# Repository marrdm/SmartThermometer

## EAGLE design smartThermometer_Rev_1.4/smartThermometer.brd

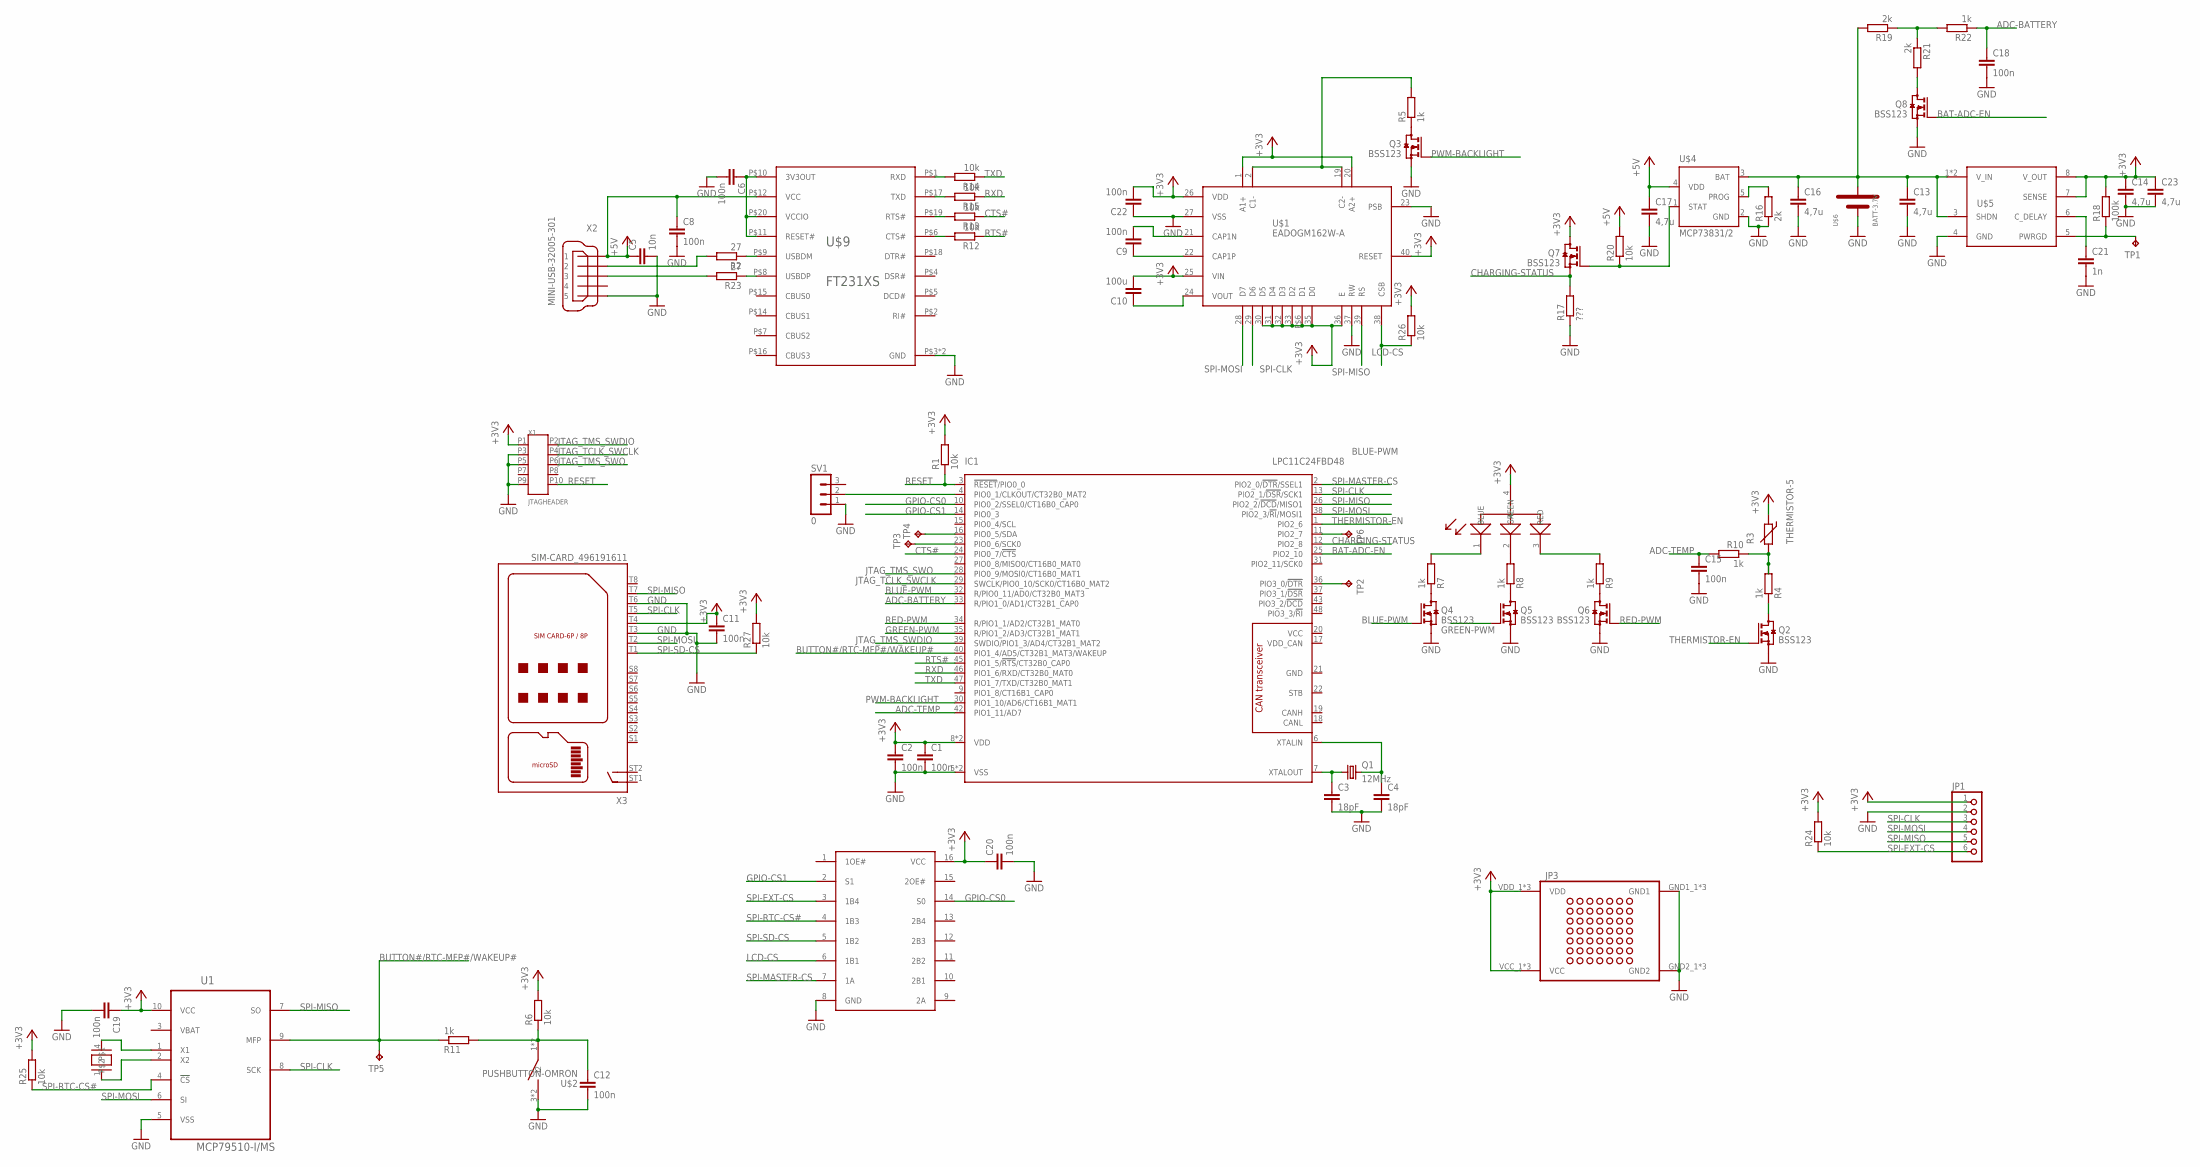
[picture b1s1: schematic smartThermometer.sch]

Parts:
C1, C2, C6, C8, C9, C11, C12, C15, C18, C19, C20, C22: 100n; C0603
C3, C4: 18pF; C0603
C5: 10n; C0603
C10: 100u; C0603
C13, C14, C16, C17, C23: 4,7u; C0805
C21: 1n; C0603
IC1: LPC11C24FBD48; SOT313-2
JP1: PINHD-1X6; 1X06
JP3: PROTOTYPE_2U_SMALL; PROTOTYPE8X6
Q1: 12MHz; HC49UP
Q2, Q3, Q4, Q5, Q6, Q7, Q8: BSS123; SOT23
R1, R6, R12, R13, R14, R15, R20, R24, R25, R26, R27: 10k; R0603
R2, R23: 27; R0603
R3: THERMISTOR-5; R-5
R4, R5, R7, R8, R9, R10, R11, R22: 1k; R0603
R16, R19, R21: 2k; R0603
R17: ???; R0603
R18: 100k; R0603
SV1: 0; MA03-1
TP1: TPTP18SQ; TP18SQ
TP2, TP3, TP4, TP5, TP6: TPTP16SQ; TP16SQ
U1: MCP79510-I/MS; SOP50P490X110-10N
U$1: EADOGM162W-A; LCD_FOOTPRINT
U$2: PUSHBUTTON-OMRON; PUSHBUTTON-OMRON-B3FS-4002P
U$3: LED-RGB-EVERLIGHT
U$4: MCP73831/2; SOT23-5L
U$5: MCP1725; SO08
U$6: BATT-3.7V; MA02-1+-
U$7: CRYSTAL-32.768KHZ-GEYER; 32.768KHZ
U$8: DEMUX-1-4-NXP; TSSOP16
U$9: FT231XS; SSOP20
X1: JTAGHEADER; HEADER10
X2: MINI-USB-32005-301; 32005-301
X3: SIM-CARD_496191611

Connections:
+3V3: C1.1, C2.1, C10.2, C11.1, C14.1, C19.1, C20.1, C22.2, C23.1, IC1.8 (VDD), IC1.44 (VDD), JP1.1, JP3.VCC_1 (VCC), JP3.VCC_2 (VCC), JP3.VCC_3 (VCC), JP3.VDD_1 (VDD), JP3.VDD_2 (VDD), JP3.VDD_3 (VDD), Q7.3 (D), R1.2, R3.1, R6.2, R18.2, R24.2, R25.2, R26.2, R27.2, U1.10 (VCC), U$1.1 (A1+), U$1.20 (A2+), U$1.25 (VIN), U$1.26 (VDD), U$1.30 (D5), U$1.31 (D4), U$1.32 (D3), U$1.33 (D2), U$1.35 (D0), U$1.36 (E), U$1.40 (RESET), U$1.P$6 (D1), U$3.4, U$5.7 (SENSE), U$5.8 (V_OUT), U$8.16 (VCC), X1.P1, X3.T4
+5V: C5.1, C8.1, C17.1, R20.2, U$4.4 (VDD), U$9.P$12 (VCC), X2.1
ADC: R3.2, R4.2, R10.1
ADC-BATTERY: C18.1, IC1.33 (R/PIO1_0/AD1/CT32B1_CAP0), R22.1
ADC-TEMP: C15.1, IC1.42 (PIO1_11/AD7), R10.2
BAT-ADC-EN: IC1.25 (PIO2_10), Q8.1 (G)
BLUE-PWM: IC1.32 (R/PIO0_11/AD0/CT32B0_MAT3), Q4.1 (G)
BUTTON#/RTC-MFP#/WAKEUP#: IC1.40 (PIO1_4/AD5/CT32B1_MAT3/WAKEUP), R11.1, TP5.TP, U1.9 (MFP)
CHARGING-STATUS: IC1.12 (PIO2_8), Q7.2 (S), R17.2
CTS#: IC1.24 (PIO0_7/!CTS!), R13.1
GND: C1.2, C2.2, C3.2, C4.2, C5.2, C6.2, C8.2, C11.2, C12.2, C13.2, C14.2, C15.2, C16.2, C17.2, C18.2, C19.2, C20.2, C21.2, C22.1, C23.2, IC1.5 (VSS), IC1.21 (GND), IC1.41 (VSS), JP1.2, JP3.GND1_1 (GND1), JP3.GND1_2 (GND1), JP3.GND1_3 (GND1), JP3.GND2_1 (GND2), JP3.GND2_2 (GND2), JP3.GND2_3 (GND2), Q2.2 (S), Q3.2 (S), Q4.2 (S), Q5.2 (S), Q6.2 (S), Q8.2 (S), R16.1, R17.1, SV1.1, U1.5 (VSS), U$1.23 (PSB), U$1.27 (VSS), U$1.37 (RW), U$2.3 (2), U$2.4 (2), U$4.2 (GND), U$5.4 (GND), U$6.2 (BAT-), U$8.8 (GND), U$9.P$3 (GND), U$9.P$13 (GND), X1.P3, X1.P5, X1.P9, X2.5, X3.T3, X3.T6
GPIO-CS0: IC1.10 (PIO0_2/SSEL0/CT16B0_CAP0), U$8.14 (S0)
GPIO-CS1: IC1.14 (PIO0_3), U$8.2 (S1)
GREEN-PWM: IC1.35 (R/PIO1_2/AD3/CT32B1_MAT1), Q5.1 (G)
JTAG_TCLK_SWCLK: IC1.29 (SWCLK/PIO0_10/SCK0/CT16B0_MAT2), X1.P4
JTAG_TMS_SWDIO: IC1.39 (SWDIO/PIO1_3/AD4/CT32B1_MAT2), X1.P2
JTAG_TMS_SWO: IC1.28 (PIO0_9/MOSI0/CT16B0_MAT1), X1.P6
LCD-CS: R26.1, U$1.38 (CSB), U$8.6 (1B1)
unnamed: R2.2, X2.2
unnamed: R23.2, X2.3
unnamed: C3.1, IC1.7 (XTALOUT), Q1.1
unnamed: C4.1, IC1.6 (XTALIN), Q1.2
unnamed: C9.2, U$1.21 (CAP1N)
unnamed: C6.1, U$9.P$10 (3V3OUT), U$9.P$11 (RESET#), U$9.P$20 (VCCIO)
unnamed: C9.1, U$1.22 (CAP1P)
unnamed: C10.1, U$1.24 (VOUT)
unnamed: Q2.3 (D), R4.1
unnamed: R5.2, U$1.2 (C1-), U$1.19 (C2-)
unnamed: Q3.3 (D), R5.1
unnamed: R2.1, U$9.P$9 (USBDM)
unnamed: R8.2, U$3.2 (GREEN)
unnamed: R7.2, U$3.1 (BLUE)
unnamed: R9.2, U$3.3 (RED)
unnamed: Q4.3 (D), R7.1
unnamed: Q5.3 (D), R8.1
unnamed: Q6.3 (D), R9.1
unnamed: IC1.4 (PIO0_1/CLKOUT/CT32B0_MAT2), SV1.2
unnamed: C13.1, C16.1, R19.2, U$4.3 (BAT), U$5.1 (V_IN), U$5.2 (V_IN), U$5.3 (SHDN), U$6.1 (BAT+)
unnamed: R16.2, U$4.5 (PROG)
unnamed: R19.1, R21.1, R22.2
unnamed: Q7.1 (G), R20.1, U$4.1 (STAT)
unnamed: R14.2, U$9.P$1 (RXD)
unnamed: R15.2, U$9.P$17 (TXD)
unnamed: C21.1, U$5.6 (C_DELAY)
unnamed: R18.1, TP1.TP, U$5.5 (PWRGD)
unnamed: R13.2, U$9.P$19 (RTS#)
unnamed: R12.2, U$9.P$6 (CTS#)
unnamed: U1.1 (X1), U$7.4
unnamed: U1.2 (X2), U$7.1
unnamed: Q8.3 (D), R21.2
unnamed: R23.1, U$9.P$8 (USBDP)
unnamed: IC1.36 (PIO3_0/!DTR!), TP2.TP
unnamed: IC1.23 (PIO0_6/SCK0), TP3.TP
unnamed: IC1.16 (PIO0_5/SDA), TP4.TP
unnamed: IC1.11 (PIO2_7), TP6.TP
unnamed: C12.1, R6.1, R11.2, U$2.1, U$2.2 (1)
PWM-BACKLIGHT: IC1.30 (PIO1_10/AD6/CT16B1_MAT1), Q3.1 (G)
RED-PWM: IC1.34 (R/PIO1_1/AD2/CT32B1_MAT0), Q6.1 (G)
RESET: IC1.3 (!RESET!/PIO0_0), R1.1, X1.P10
RTS#: IC1.45 (PIO1_5/!RTS!/CT32B0_CAP0), R12.1
RXD: IC1.46 (PIO1_6/RXD/CT32B0_MAT0), R15.1
SPI-CLK: IC1.13 (PIO2_1/!DSR!/SCK1), JP1.3, U1.8 (SCK), U$1.29 (D6), X3.T5
SPI-EXT-CS: JP1.6, R24.1, U$8.3 (1B4)
SPI-MASTER-CS: IC1.2 (PIO2_0/!DTR!/SSEL1), U$8.7 (1A)
SPI-MISO: IC1.26 (PIO2_2/!DCD!/MISO1), JP1.5, U1.7 (SO), U$1.39 (RS), X3.T7
SPI-MOSI: IC1.38 (PIO2_3/!RI!/MOSI1), JP1.4, U1.6 (SI), U$1.28 (D7), X3.T2
SPI-RTC-CS#: R25.1, U1.4 (!CS), U$8.4 (1B3)
SPI-SD-CS: R27.1, U$8.5 (1B2), X3.T1
THERMISTOR-EN: IC1.1 (PIO2_6), Q2.1 (G)
TXD: IC1.47 (PIO1_7/TXD/CT32B0_MAT1), R14.1

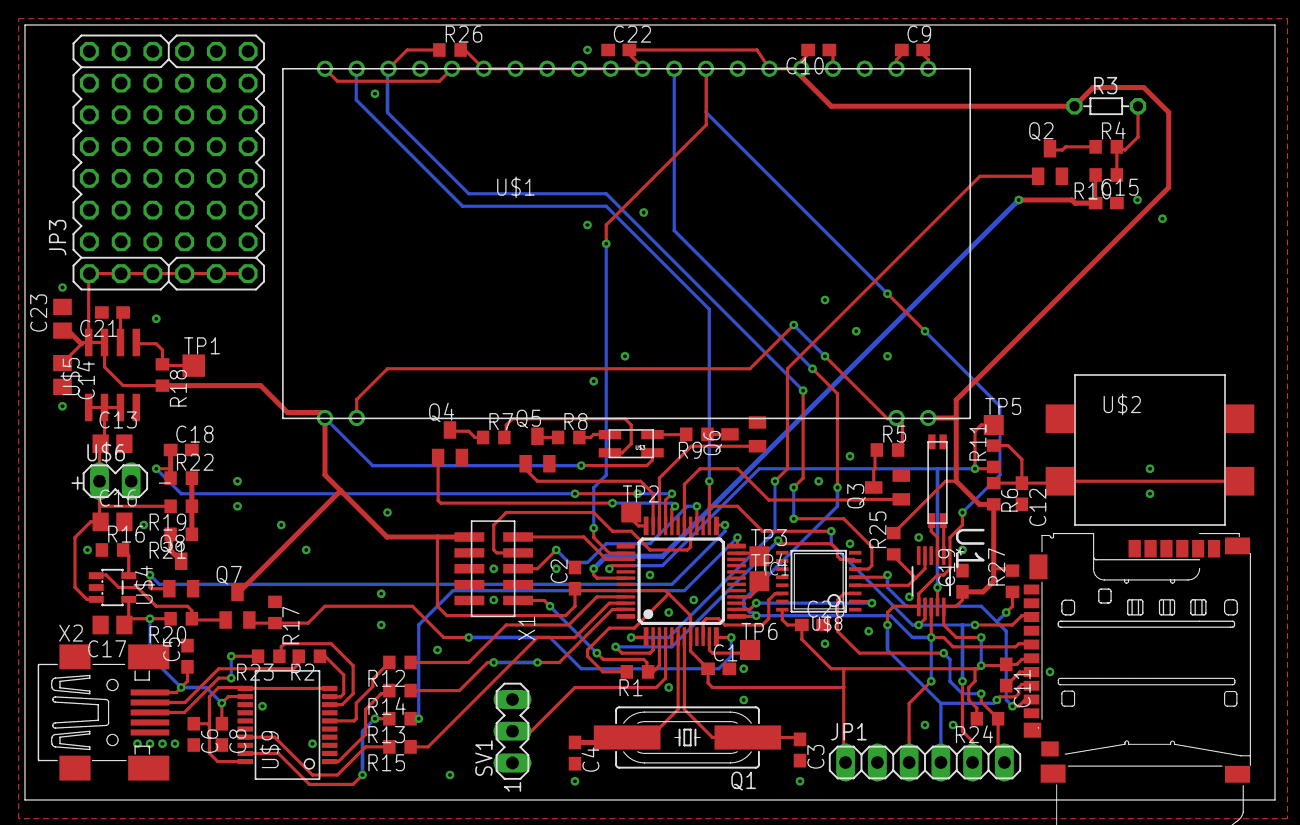
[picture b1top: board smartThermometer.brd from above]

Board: 2 copper layers, 100.0 x 62.0 mm, 80 parts (0 on the bottom side), 70 nets.

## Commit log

2015-03-03 Added Eagle schematics
2015-03-03 tweak schematic
2015-03-03 Word Document
2015-03-04 Added SmartThermometer_Rev_2. Fixed broken footplrints
2015-03-06 Added Software, pwm test
2015-03-09 Improved pwm
2015-03-13 pwm update
2015-03-13 Added interrupt code for timer, UART, button and AD
2015-03-13 Added timer 32B0 setup code
2015-03-13 added basic UART buffer
    buffer is currently non-functional
2015-03-16 Fixed timer driven ADC
2015-03-18 Changed code to 16 bit timer and started SPI code
2015-03-19 UART working
2015-03-19 Added .gitignore
2015-03-19 Updated .gitignore
2015-03-19 Cleaned .metadata
2015-03-19 Added Eagle and C ignores to .gitignore
2015-03-19 SPI and LCD code
2015-03-23 float2str working, added temp convestion to C
2015-03-23 Added SPI test code
2015-03-23 Moved adc code, added temp.c, fixed bug in str.c
2015-03-24 SPI testing
2015-03-24 lcd init code
2015-03-24 allow pwm duty cycle to be 0
2015-03-25 Fixed LCD code
2015-03-25 Fixed display kelvin
2015-03-25 moved prints to the LCD to temp.c
